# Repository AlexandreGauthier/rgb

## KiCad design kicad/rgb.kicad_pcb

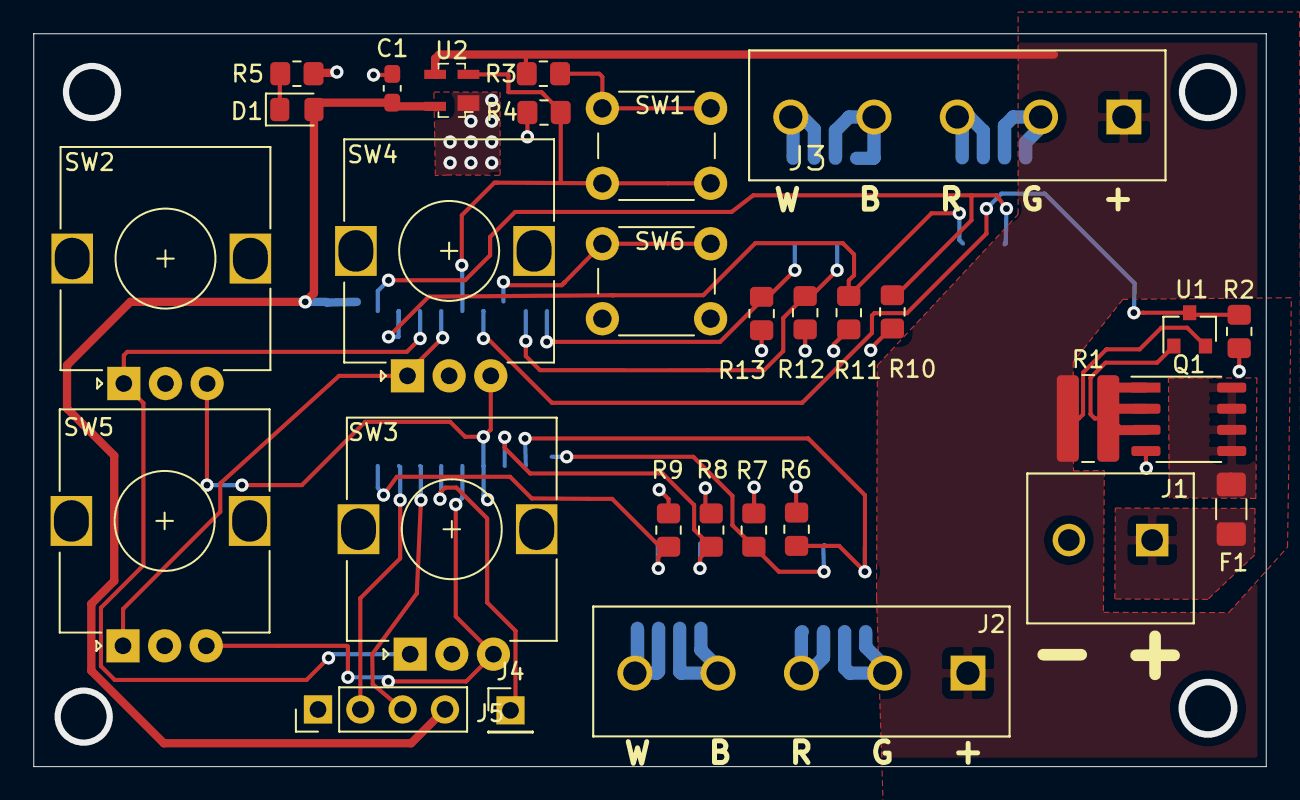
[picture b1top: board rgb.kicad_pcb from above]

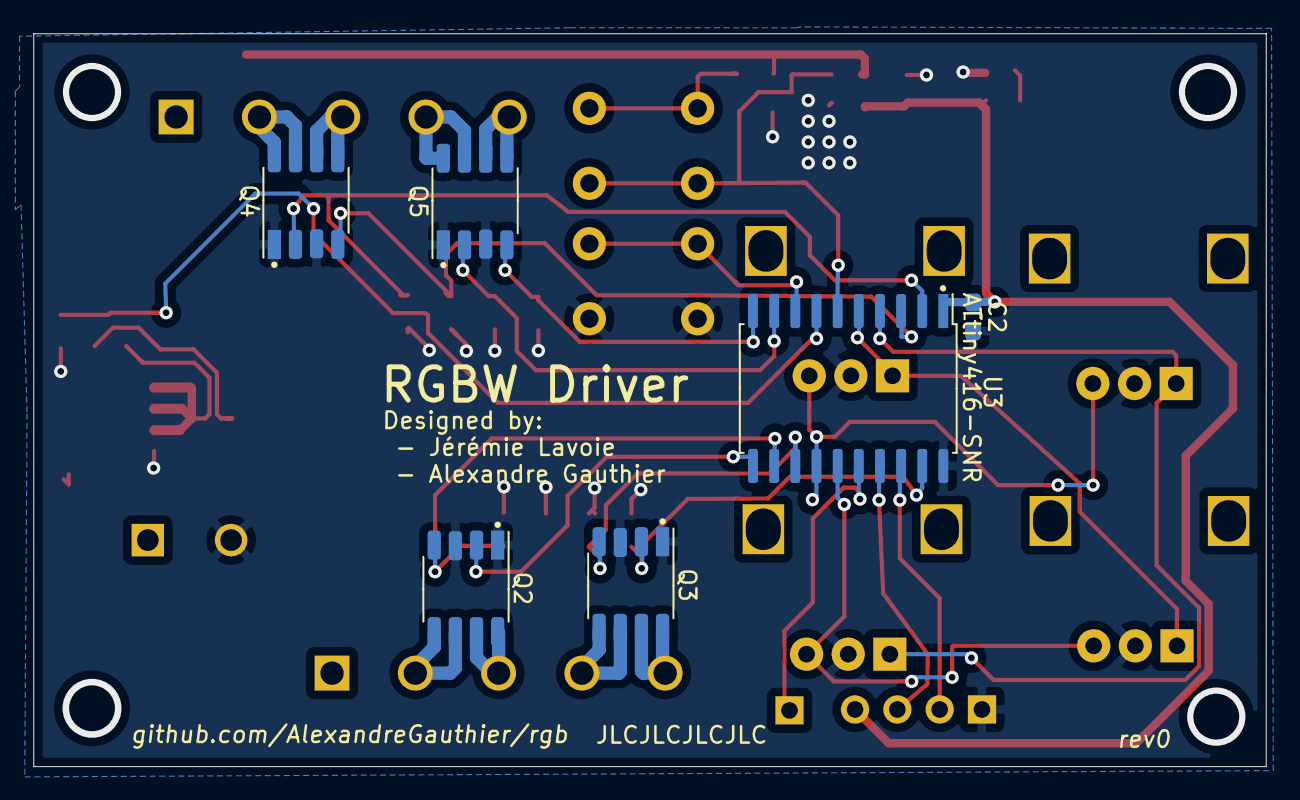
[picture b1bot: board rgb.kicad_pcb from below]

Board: 2 copper layers, 74.0 x 44.0 mm, 36 parts (6 on the bottom side), 34 nets.

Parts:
C1: 470 nF; C_0603_1608Metric_Pad1.08x0.95mm_HandSolder
C2: 100 nF; C_0603_1608Metric_Pad1.08x0.95mm_HandSolder
D1: 732-4987-2-ND; LED_0805_2012Metric_Pad1.15x1.40mm_HandSolder
F1: 0685H9200-01; Fuse_1206_3216Metric_Pad1.42x1.75mm_HandSolder
J1: 1935776; CUI_TB001-500-02BE
J2, J3: 102-6164-ND; CUI_TB003-500-P05BE
J4: Conn_01x04; PinHeader_1x01_P2.54mm_Vertical
J5: Conn_01x02; PinHeader_1x04_P2.54mm_Vertical
Q1: Si4101DY
Q2, Q3, Q4, Q5: DMG9926USD; DMG9926USD_Handsolder
R1: 5 mΩ; R_1020_2550Metric_Pad1.33x5.20mm_HandSolder
R2: 10 kΩ; R_0805_2012Metric_Pad1.20x1.40mm_HandSolder
R3: 110 kΩ; R_0805_2012Metric_Pad1.20x1.40mm_HandSolder
R4, R6, R7, R8, R9, R10, R11, R12, R13: 50 kΩ; R_0805_2012Metric_Pad1.20x1.40mm_HandSolder
R5: 1 kΩ; R_0805_2012Metric_Pad1.20x1.40mm_HandSolder
SW1, SW6: 450-1642-ND; SW_PUSH_6mm_H13mm
SW2, SW3, SW4, SW5: PEC12R-4220F-N0024; rotary encoder
U1: ZXCT1109; SOT-23
U2: MIC5203-5.0; SOT-143-4
U3: ATtiny416-SNR; ATTINY416-SNR

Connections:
+5V: C1.1, C2.1, D1.2, J5.4, U2.4, U3.1
+12V: J2.1, J3.1, R1.2, R3.2, U1.2, U2.3
/DRAIN_1: J2.2, Q2.D2
/DRAIN_2: J2.3, Q2.D1
/DRAIN_3: J2.4, Q3.D2
/DRAIN_4: J2.5, Q3.D1
/DRAIN_5: J3.2, Q4.D1
/DRAIN_6: J3.3, Q4.D2
/DRAIN_7: J3.4, Q5.D1
/DRAIN_8: J3.5, Q5.D2
/PWM_1: Q2.G2, R6.1, U3.12
/PWM_2: Q2.G1, R7.1, U3.11
/PWM_3: Q3.G2, R8.1, U3.13
/PWM_4: Q3.G1, R9.1, U3.19
/PWM_5: Q4.G1, R10.1, U3.2
/PWM_6: Q4.G2, R11.1, U3.3
/PWM_7: Q5.G1, R12.1, U3.9
/PWM_8: Q5.G2, R13.1, U3.10
/PWR_EN: R4.1, SW1.1, U2.2, U3.6
/RESET: J4.1, U3.16
/SENSE: R2.1, U1.3, U3.7
/SW6: SW6.1, U3.8
/SW_A1: SW2.A, SW3.A, U3.4
/SW_A2: SW4.A, SW5.A, U3.5
/SW_B1: SW2.B, SW4.B, U3.14
/SW_B2: SW3.B, SW5.B, U3.15
/TWI_SCL: J5.2, U3.18
/TWI_SDA: J5.3, U3.17
GND: C1.2, C2.2, J1.2, J5.1, Q1.G, Q2.S1, Q2.S2, Q3.S1, Q3.S2, Q4.S1, Q4.S2, Q5.S1, Q5.S2, R2.2, R4.2, R5.2, R6.2, R7.2, R8.2, R9.2, R10.2, R11.2, R12.2, R13.2, SW2.C, SW3.C, SW4.C, SW5.C, SW6.2, U2.1, U3.20
unnamed: D1.1, R5.1
unnamed: F1.1, Q1.D
unnamed: F1.2, J1.1
unnamed: Q1.S, R1.1, U1.1
unnamed: R3.1, SW1.2

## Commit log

2020-12-24 Starting schematics
2020-12-27 changed mosfets
2020-12-27 Added power supply
2020-12-27 Cleaned up DC-DC
2020-12-27 driver circuits
2020-12-28 ATTINY216
2020-12-29 Schematics work
2020-12-30 Connectors / protection
2020-12-30 footprints
2020-12-31 Changed dc-dc
2020-12-31 bulk capacitor
2020-12-31 layout start
2021-01-01 ground / power planes
2021-01-02 more power planes
2021-01-02 removed outdated spice
2021-01-02 footprint details
2021-01-02 trace routing
2021-01-02 adjustments
2021-01-03 power planes
2021-01-03 pcb layout + mounting
2021-01-03 New PCB formfactor
2021-01-04 minor layout changes
2021-01-04 dcdc layout
2021-01-04 this dummy wants his name spelled right
2021-01-04 datasheets and model numbers
2021-01-06 changed vin connector, touchups
2021-01-07 layout done
2021-01-07 rev0
2021-01-09 added drill files
2021-01-09 created firmware solution
2021-01-30 minor changes
2021-01-30 program structure
2021-01-31 rev1
2021-03-16 starting rev1
